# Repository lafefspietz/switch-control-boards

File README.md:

# [Switch Control Boards](https://github.com/lafefspietz/switch-control-boards)

Generic control panel circuit boards for building physical human computer interfaces into control systems based on the [MEMSDuino](https://github.com/lafefspietz/MEMSduino/) open source repository.  That system is designed for controlling the 90 volt control lines of a network of MEMS(Micro Electrical Mechanical System) based radio frequency(RF) switches which are used for calibration and testing of measurement systems for the development of quantum computing technology.  The 90 volt signals in that system are controlled using a set of cheap 5 volt electromechanical relays which are from the telecommunications industry.

This project begins with converting all the Altium files into KiCAD and then making various forks to those boards. It is being used as an excuse to learn KiCAD in order to switch from Altium to KiCAD in general by porting the circuit boards from MEMSDuino into KiCAD and then making useful modifications.

## Arduino to Headers Board

This board connects between the Arduino UNO and a set of headers which go to the various other circuit boards.

 - [arduino-to-headers-shield.kicad_sch](arduino-to-headers-shield.kicad_sch)
 - [arduino-to-headers-shield.kicad_pcb](arduino-to-headers-shield.kicad_pcb)
 - [arduino-to-headers-shield.kicad_pro](arduino-to-headers-shield.kicad_pro)

## 6 State Control Board

Control board with 6 buttons and 6 programmable RGB LED indicator lights.

 - [6button-6neopixel.kicad_pcb](6button-6neopixel.kicad_pcb)
 - [6button-6neopixel.kicad_pro](6button-6neopixel.kicad_pro)
 - [6button-6neopixel.kicad_sch](6button-6neopixel.kicad_sch)

## 9 State Control Board

Control board with 9 buttons and 9 programmable RGB LED indicator lights.

 - [9button-9neopixel.kicad_pcb](9button-9neopixel.kicad_pcb)
 - [9button-9neopixel.kicad_pro](9button-9neopixel.kicad_pro)
 - [9button-9neopixel.kicad_sch](9button-9neopixel.kicad_sch)
 
## DB25 Relay Control Board  

This board uses a set of 5 volt control lines from the Arduino UNO to control a set of electromechanical relays which turn connect a high voltge(90 V) line to any of the  pins on the DB25 connector.

 - [DB25-relay-HV-control.kicad_pcb](DB25-relay-HV-control.kicad_pcb)
 - [DB25-relay-HV-control.kicad_pro](DB25-relay-HV-control.kicad_pro)
 - [DB25-relay-HV-control.kicad_sch](DB25-relay-HV-control.kicad_sch)

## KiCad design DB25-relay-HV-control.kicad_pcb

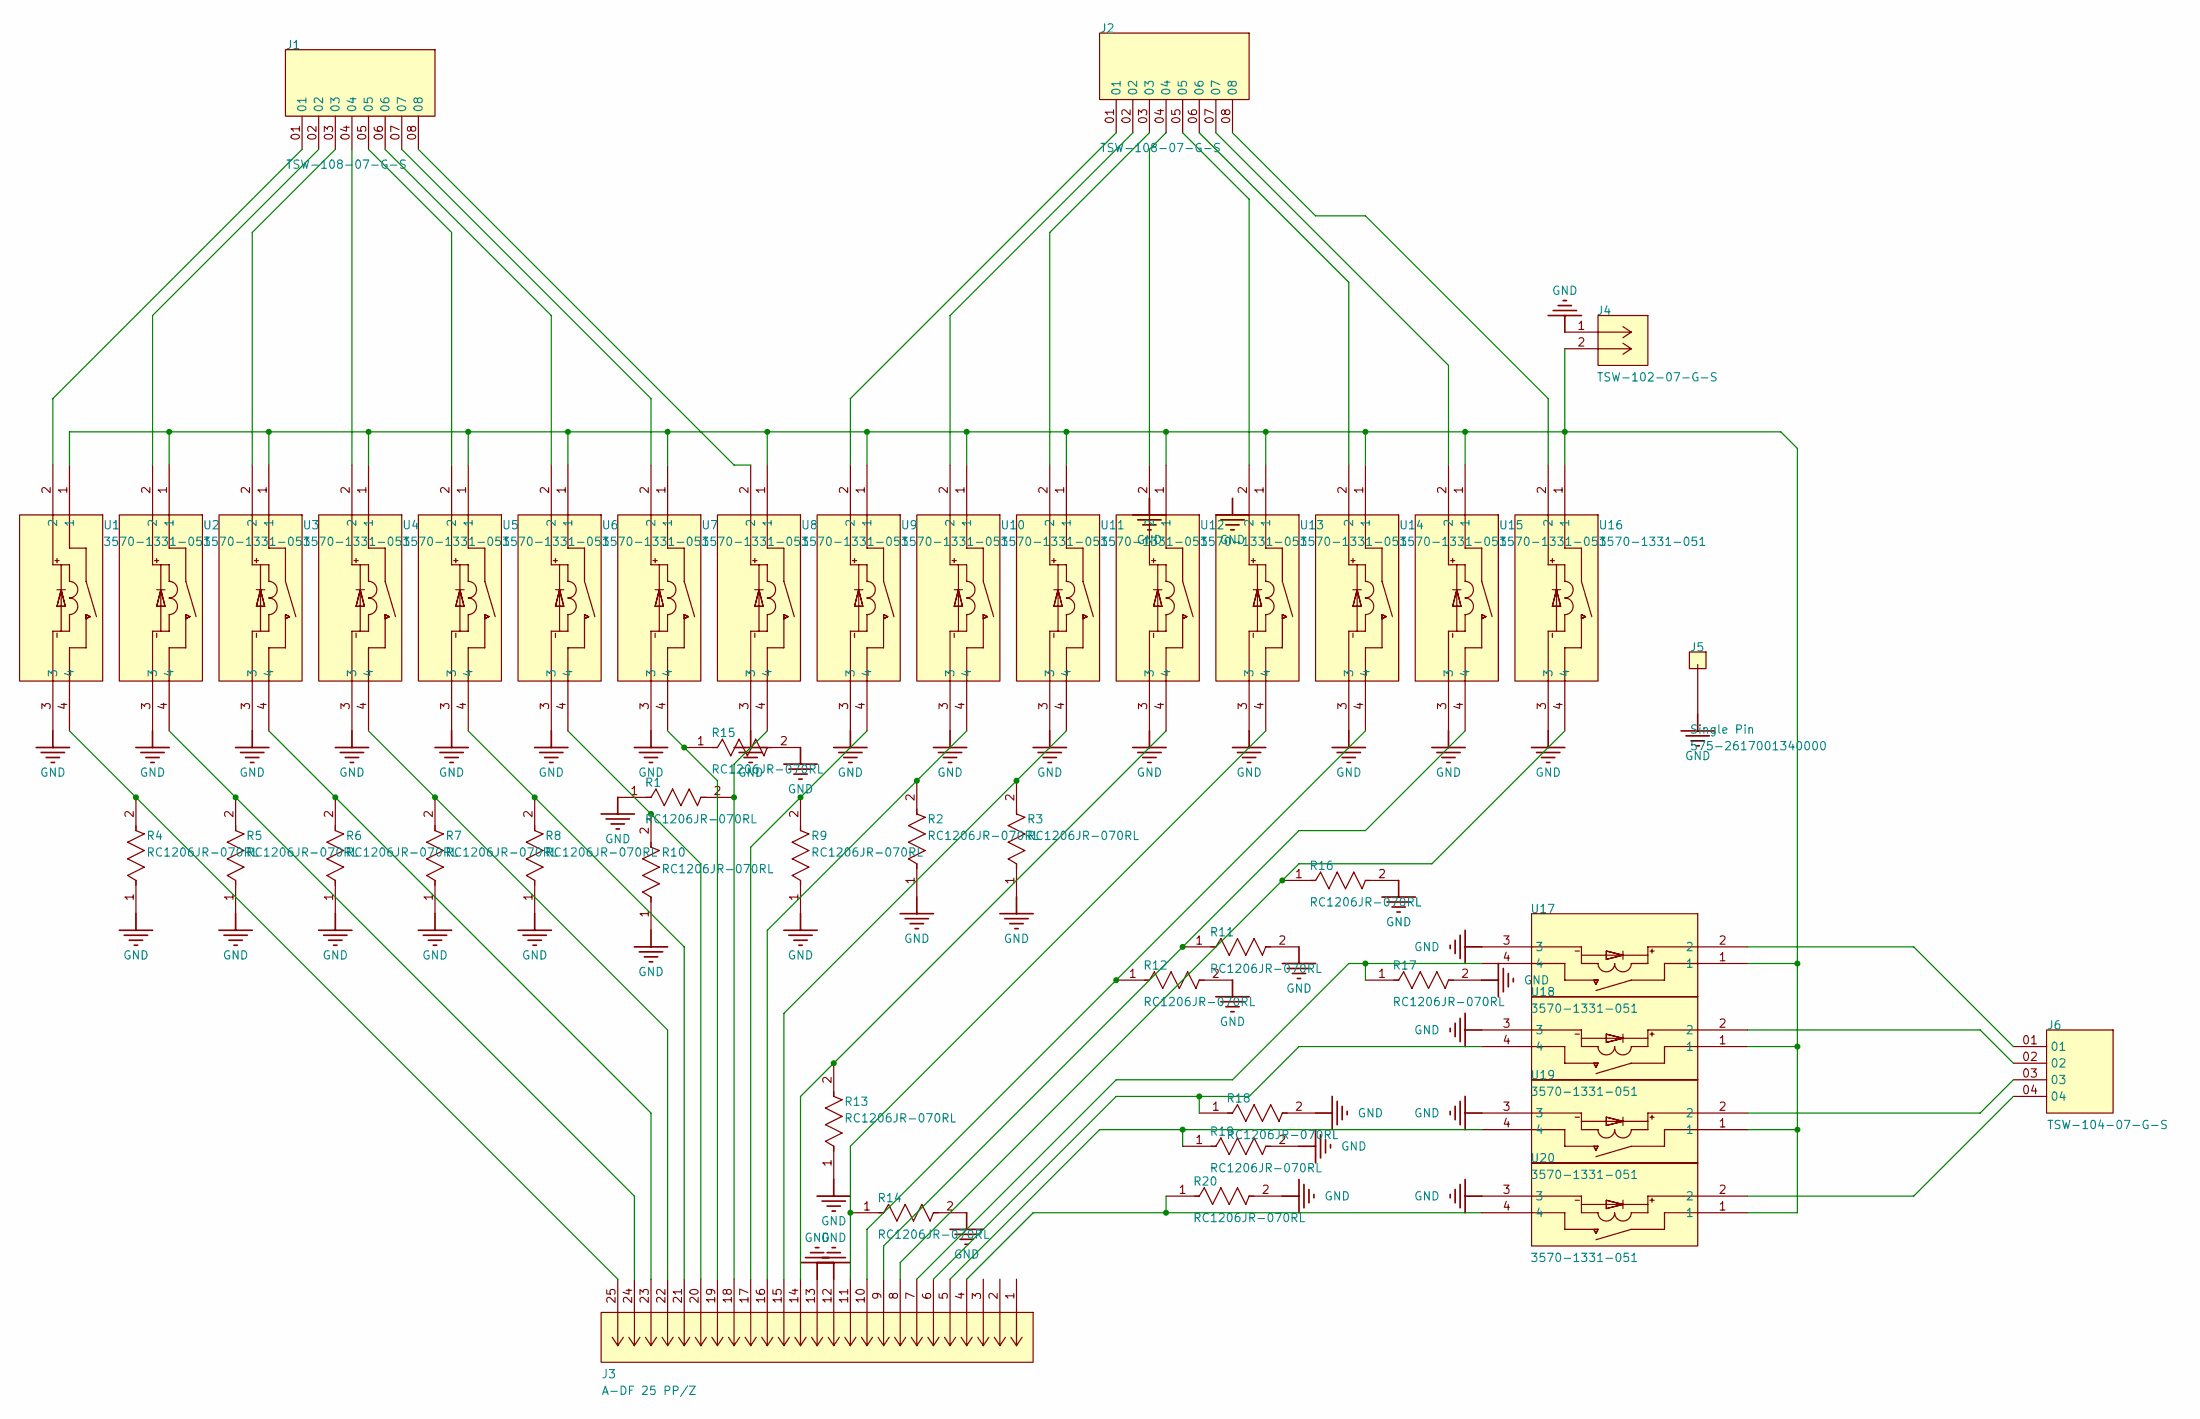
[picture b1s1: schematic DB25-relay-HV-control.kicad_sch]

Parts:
J1, J2: TSW-108-07-G-S; SAMTEC_TSW-108-07-G-S
J3: A-DF 25 PP/Z; CONN_A-DF 25 PPZ_ASM; MANUFACTURER_PART_NUMBER A-DF 25 PP/Z
J4: TSW-102-07-G-S; CON2_1X2_TU_TSW; MANUFACTURER_PART_NUMBER TSW-102-07-G-S
J5: Single Pin; Single PC Pin
J6: TSW-104-07-G-S; SAMTEC_TSW-104-07-G-S
R1, R2, R3, R4, R5, R6, R7, R8, R9, R10, R11, R12, R13, R14, R15, R16, R17, R18, R19, R20: RC1206JR-070RL; FP-RC1206-MFG; VOLTAGE RATING 200V; POWER RATING 0.25W; MANUFACTURER PART NUMBER RC1206JR-070RL; DIGIKEY DESCRIPTION RES SMD 0 OHM JUMPER 1/4W 1206
U1, U2, U3, U4, U5, U6, U7, U8, U9, U10, U11, U12, U13, U14, U15, U16, U17, U18, U19, U20: 3570-1331-051; SIP_3570-1331_COM; MANUFACTURER_PART_NUMBER 3570-1331-051

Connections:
GND: J3.12, J3.13, J4.1, J5.1, R1.1, R2.1, R3.1, R4.1, R5.1, R6.1, R7.1, R8.1, R9.1, R10.1, R11.2, R12.2, R13.1, R14.2, R15.2, R16.2, R17.2, R18.2, R19.2, R20.2, U1.3, U2.3, U3.3, U4.3, U5.3, U6.3, U7.3, U8.3, U9.3, U10.3, U11.3, U12.3, U13.3, U14.3, U15.3, U16.3, U17.3, U18.3, U19.3, U20.3
NetJ1_01: J1.01, U1.2
NetJ1_02: J1.02, U2.2
NetJ1_03: J1.03, U3.2
NetJ1_04: J1.04, U4.2
NetJ1_05: J1.05, U5.2
NetJ1_06: J1.06, U6.2
NetJ1_07: J1.07, U7.2
NetJ1_08: J1.08, U8.2
NetJ2_01: J2.01, U9.2
NetJ2_02: J2.02, U10.2
NetJ2_03: J2.03, U11.2
NetJ2_04: J2.04, U12.2
NetJ2_05: J2.05, U13.2
NetJ2_06: J2.06, U14.2
NetJ2_07: J2.07, U15.2
NetJ2_08: J2.08, U16.2
NetJ3_4: J3.4, R20.1, U20.4
NetJ3_5: J3.5, R19.1, U19.4
NetJ3_6: J3.6, R18.1, U18.4
NetJ3_7: J3.7, R17.1, U17.4
NetJ3_8: J3.8, R16.1, U16.4
NetJ3_9: J3.9, R11.1, U15.4
NetJ3_10: J3.10, R12.1, U14.4
NetJ3_11: J3.11, R14.1, U13.4
NetJ3_14: J3.14, R13.2, U12.4
NetJ3_15: J3.15, R3.2, U11.4
NetJ3_16: J3.16, R2.2, U10.4
NetJ3_17: J3.17, R9.2, U9.4
NetJ3_18: J3.18, R1.2, U8.4
NetJ3_19: J3.19, R15.1, U7.4
NetJ3_20: J3.20, R10.2, U6.4
NetJ3_21: J3.21, R8.2, U5.4
NetJ3_22: J3.22, R7.2, U4.4
NetJ3_23: J3.23, R6.2, U3.4
NetJ3_24: J3.24, R5.2, U2.4
NetJ3_25: J3.25, R4.2, U1.4
NetJ4_2: J4.2, U1.1, U2.1, U3.1, U4.1, U5.1, U6.1, U7.1, U8.1, U9.1, U10.1, U11.1, U12.1, U13.1, U14.1, U15.1, U16.1, U17.1, U18.1, U19.1, U20.1
NetJ6_01: J6.01, U17.2
NetJ6_02: J6.02, U18.2
NetJ6_03: J6.03, U19.2
NetJ6_04: J6.04, U20.2

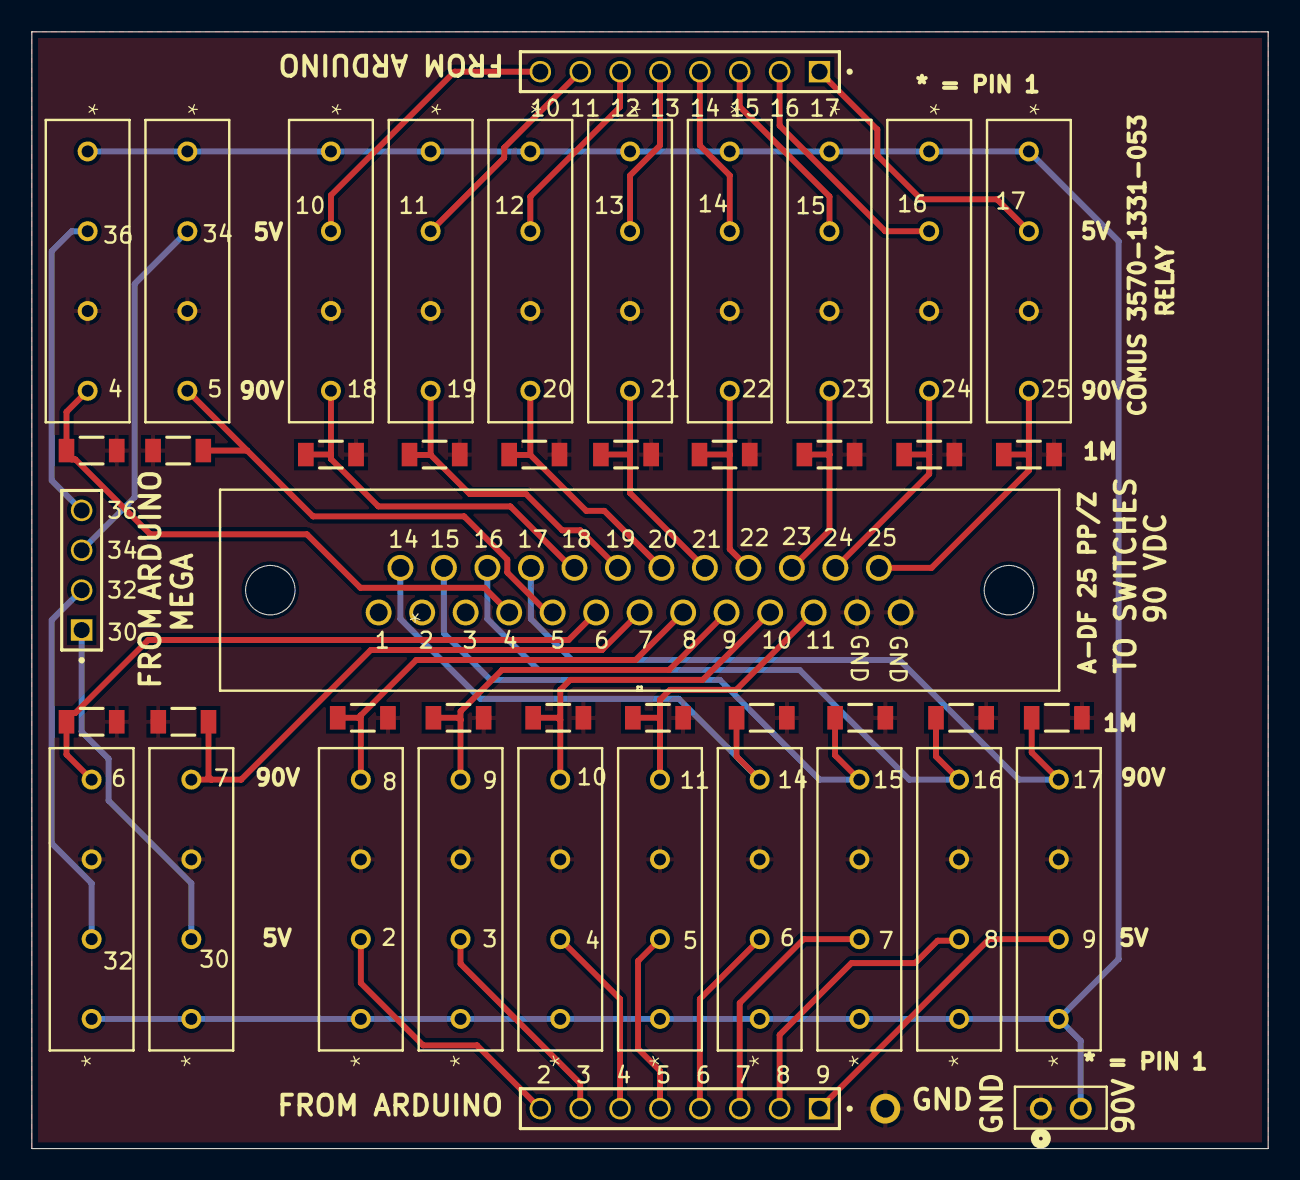
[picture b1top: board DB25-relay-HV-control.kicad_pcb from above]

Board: 2 copper layers, 78.7 x 71.1 mm, 46 parts (0 on the bottom side), 42 nets.

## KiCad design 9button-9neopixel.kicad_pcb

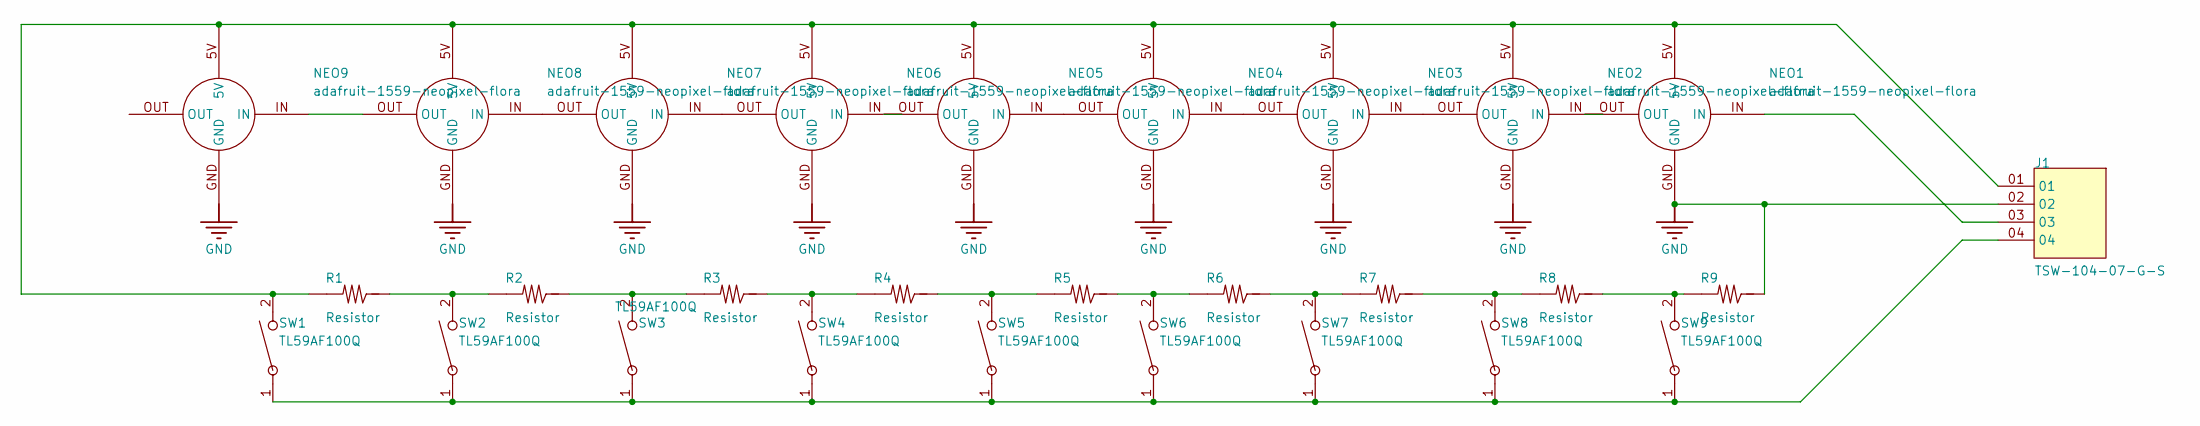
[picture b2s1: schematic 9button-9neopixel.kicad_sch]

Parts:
J1: TSW-104-07-G-S; SAMTEC_TSW-104-07-G-S
NEO1, NEO2, NEO3, NEO4, NEO5, NEO6, NEO7, NEO8, NEO9: adafruit-1559-neopixel-flora
R1, R2, R3, R4, R5, R6, R7, R8, R9: Resistor; thruhole resistor
SW1, SW2, SW3, SW4, SW5, SW6, SW7, SW8, SW9: TL59AF100Q; SW_TL59AF100Q_EWI; MANUFACTURER_PART_NUMBER TL59AF100Q

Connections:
NetJ1_01: J1.01, NEO1.5V, NEO2.5V, NEO3.5V, NEO4.5V, NEO5.5V, NEO6.5V, NEO7.5V, NEO8.5V, NEO9.5V, R1.2, SW1.2
NetJ1_03: J1.03, NEO1.IN
NetJ1_04: J1.04, SW1.1, SW2.1, SW3.1, SW4.1, SW5.1, SW6.1, SW7.1, SW8.1, SW9.1
NetNEO1_OUT: NEO1.OUT, NEO2.IN
NetNEO2_OUT: NEO2.OUT, NEO3.IN
NetNEO3_OUT: NEO3.OUT, NEO4.IN
NetNEO4_OUT: NEO4.OUT, NEO5.IN
NetNEO5_OUT: NEO5.OUT, NEO6.IN
NetNEO6_OUT: NEO6.OUT, NEO7.IN
NetNEO7_OUT: NEO7.OUT, NEO8.IN
NetNEO8_OUT: NEO8.OUT, NEO9.IN
NetR1_1: R1.1, R2.2, SW2.2
NetR2_1: R2.1, R3.2, SW3.2
NetR3_1: R3.1, R4.2, SW4.2
NetR4_1: R4.1, R5.2, SW5.2
NetR5_1: R5.1, R6.2, SW6.2
NetR6_1: R6.1, R7.2, SW7.2
NetR7_1: R7.1, R8.2, SW8.2
NetR8_1: R8.1, R9.2, SW9.2

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
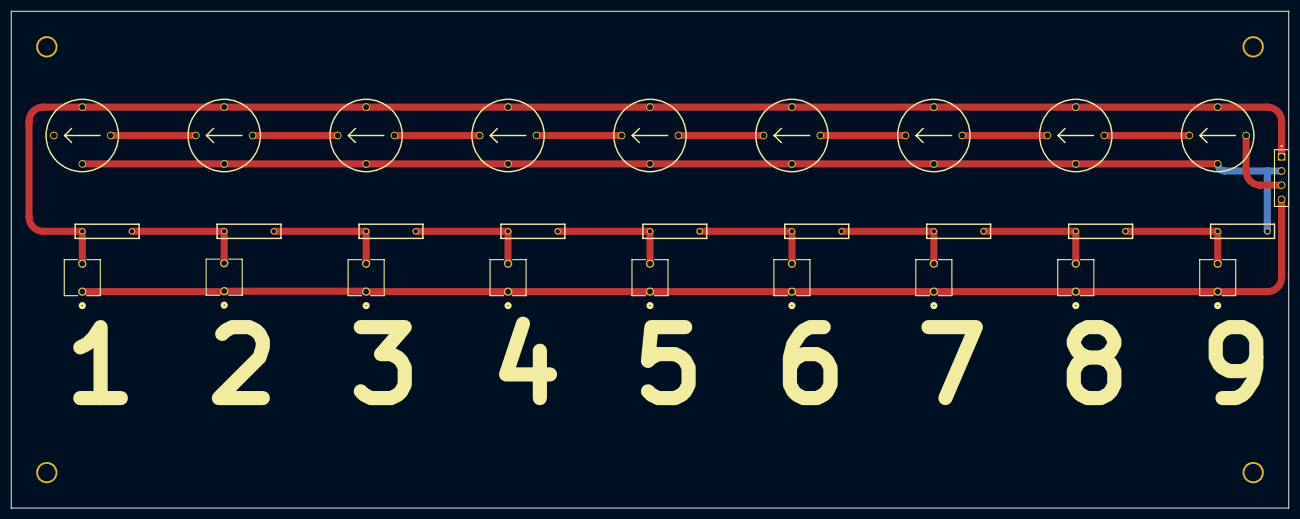
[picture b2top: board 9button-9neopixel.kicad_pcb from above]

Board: 2 copper layers, 228.6 x 88.9 mm, 28 parts (0 on the bottom side), 20 nets.

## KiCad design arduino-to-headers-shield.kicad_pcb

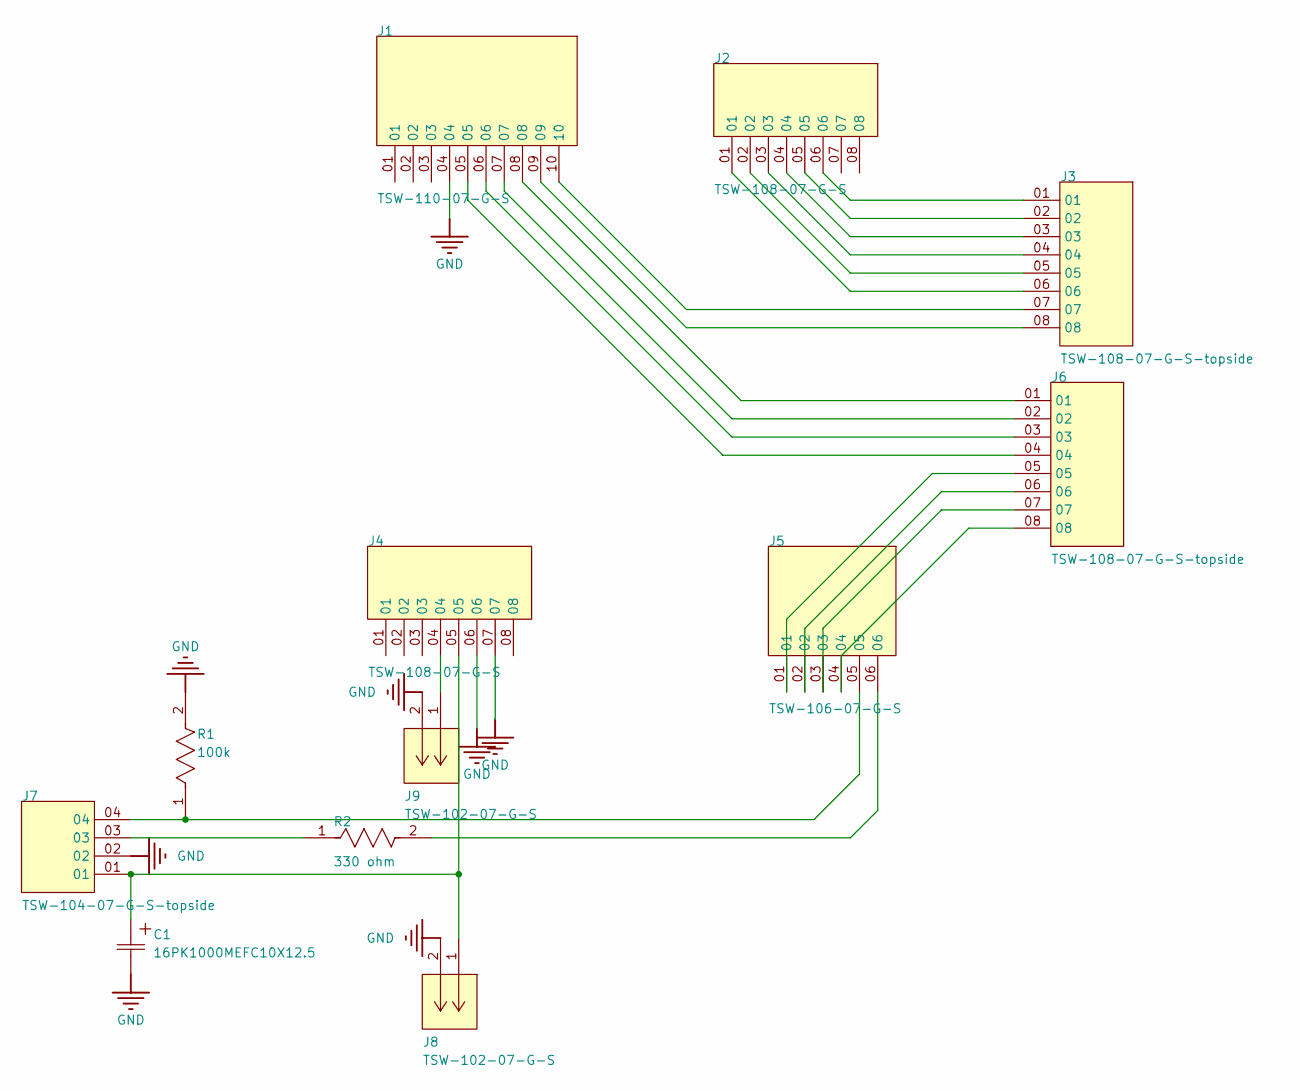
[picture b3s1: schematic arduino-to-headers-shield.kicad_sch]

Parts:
C1: 16PK1000MEFC10X12.5; CAP_PKPZ_10X12P5_LOW_RUB; MANUFACTURER_PART_NUMBER 16PK1000MEFC10X12.5
J1: TSW-110-07-G-S; SAMTEC_TSW-110-07-G-S
J2, J4: TSW-108-07-G-S; SAMTEC_TSW-108-07-G-S
J3, J6: TSW-108-07-G-S-topside; SAMTEC_TSW-108-07-G-S-topside
J5: TSW-106-07-G-S; SAMTEC_TSW-106-07-G-S
J7: TSW-104-07-G-S-topside; SAMTEC_TSW-104-07-G-S-topside
J8, J9: TSW-102-07-G-S; TSW-102-07-G-S-topside; MANUFACTURER_PART_NUMBER TSW-102-07-G-S
R1: 100k; FP-RLR07-MFG; POWER RATING 250mW; TOLERANCE 1%
R2: 330 ohm; FP-RLR07-MFG; POWER RATING 250mW; TOLERANCE 1%

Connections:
GND: C1.2, J1.04, J4.06, J4.07, J7.02, J8.2, J9.2, R1.2
NetC1_1: C1.1, J4.05, J7.01, J8.1
NetJ1_05: J1.05, J6.04
NetJ1_06: J1.06, J6.03
NetJ1_07: J1.07, J6.02
NetJ1_08: J1.08, J6.01
NetJ1_09: J1.09, J3.08
NetJ1_10: J1.10, J3.07
NetJ2_01: J2.01, J3.06
NetJ2_02: J2.02, J3.05
NetJ2_03: J2.03, J3.04
NetJ2_04: J2.04, J3.03
NetJ2_05: J2.05, J3.02
NetJ2_06: J2.06, J3.01
NetJ4_04: J4.04, J9.1
NetJ5_01: J5.01, J6.05
NetJ5_02: J5.02, J6.06
NetJ5_03: J5.03, J6.07
NetJ5_04: J5.04, J6.08
NetJ5_05: J5.05, J7.04, R1.1
NetJ5_06: J5.06, R2.2
NetJ7_03: J7.03, R2.1

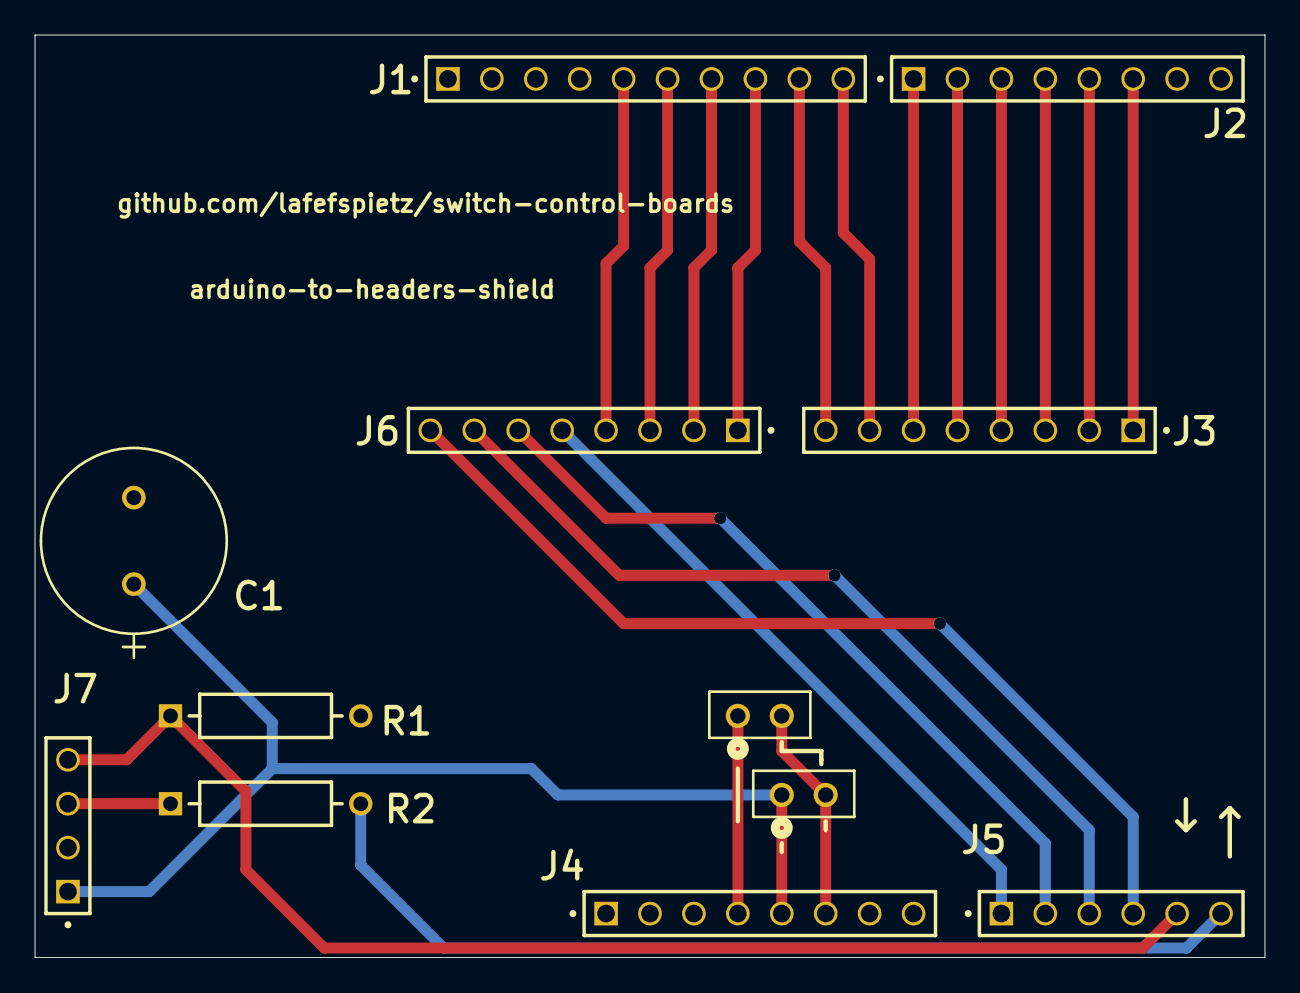
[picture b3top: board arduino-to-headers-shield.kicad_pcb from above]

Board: 2 copper layers, 71.1 x 53.3 mm, 12 parts (0 on the bottom side), 22 nets.

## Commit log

2025-12-19 cloned boards from Altium to KiCAD
2025-12-19 started on SP3TECAL rf board

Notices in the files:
parts and their libraries:
COPYRIGHT: Copyright (C) 2024 Ultra Librarian. All rights reserved.
